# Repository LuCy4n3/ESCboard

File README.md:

# ESC_HS

This repository contains two generations of the ESC project. The repository name
remains `ESC_HS`. The original project names `ESC_HS` and `ESC_HF` are unchanged.

Both generations are experimental development builds. v1 includes firmware for
bench research and hardware bring-up; v2 is a hardware design with firmware still
to be implemented. See the [experimental build notes](v1/ESC_HS/EXPERIMENTAL_BUILD.md)
for the current v1 diagnostic configuration and validation limits.

| Version | Project | Contents | Documentation |
| --- | --- | --- | --- |
| v1 | `ESC_HS` | STSPIN32G4/STM32G431 firmware, matching KiCad design, capture tools and BOM. | [v1 usage](v1/ESC_HS/README.md) |
| v2 | `ESC_HF` | STM32H750 + DRV8323 KiCad hardware design and component libraries. | [v2 hardware](v2/ESC_HF/README.md) |

```text
ESC_HS/                         existing Git repository
  .gitignore                    shared rules for both versions
  README.md                     version index
  v1/
    ESC_HS/                     original CubeIDE project name
      Core/
      Drivers/
      esc_design/
      hardware/                 v1 BOM and review findings
      tools/
      ESC_HS.ioc
      README.md
  v2/
    ESC_HF/                     original hardware project name
      ESC_HF/                   KiCad project, schematic, PCB and Gerbers
      componente/               component symbols and footprints
      README.md
```

## Using v1

Import `v1/ESC_HS/` as the existing `ESC_HS` project in STM32CubeIDE. If an IDE
workspace still points to the old repository root, remove that workspace entry
without deleting files, then import the new directory. The project name remains
`ESC_HS`, so its workspace-relative build configuration can keep using that name.

Run the commands in the v1 usage guide from `v1/ESC_HS/`. Its schematic and BOM
links remain relative to that project directory:

- [BOM and design findings](v1/ESC_HS/hardware/BOM.md)
- [Excel BOM](v1/ESC_HS/hardware/outputs/esc_hs_bom/BOM.xlsx)
- [Grouped BOM CSV](v1/ESC_HS/hardware/BOM.csv)

The preserved v1 firmware can start with a 2000 RPM target after power-up. Review
the commissioning instructions and configuration before powering the bridge.

## Using v2

Open `v2/ESC_HF/ESC_HF/ESC_HF.kicad_pro` in KiCad. The nested hardware project and
the component-library directory retain their original names and contents.
This version currently contains hardware files. The v1 BOM and firmware describe
a different controller and power-stage design; v2 needs its own component export
and firmware implementation.

## Git organization

Both versions share this repository's existing history. Run Git commands from
this directory. Generated build files, KiCad backups/caches, source snapshots and
captures stay local under their respective version folders and are ignored.

The reorganization preserves project sources, original design files and local
build outputs. It does not change firmware behavior or hardware components.

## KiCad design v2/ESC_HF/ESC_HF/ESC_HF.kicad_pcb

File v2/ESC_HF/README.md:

# ESC_HF

**ESC v2.** The project name remains `ESC_HF`. This hardware generation uses
STM32H750 and DRV8323, with a separate schematic and PCB from
[ESC_HS v1](../../v1/ESC_HS/README.md).

This is an experimental hardware development build. Its controller and peripheral
mapping need a dedicated firmware implementation and bench validation.

## Contents

| Path | Contents |
| --- | --- |
| `ESC_HF/ESC_HF.kicad_pro` | KiCad project. |
| `ESC_HF/ESC_HF.kicad_sch` | Schematic. |
| `ESC_HF/ESC_HF.kicad_pcb` | PCB layout. |
| `componente/` | Component-library resources supplied with the design. |
| `ESC_HF/grb/`, `ESC_HF/grb.zip` | Existing manufacturing exports. |

Open `ESC_HF/ESC_HF.kicad_pro` in KiCad. Review the selected library paths when
opening the project on a different machine. Bundled 3D model links use
`${KIPRJMOD}/../componente/` so they resolve from this KiCad project after the move.
Manufacturing exports are retained
as supplied; regenerate them from the intended PCB revision before fabrication.

This directory currently contains hardware design files. It does not contain a
dedicated v2 firmware project or a newly generated v2 BOM. The v1 firmware targets
STSPIN32G4/STM32G431 and must be ported for the v2 controller and peripheral mapping.

The original schematic, circuit/layout, component resources and local backups
were preserved during version organization. Only the old absolute 3D model links
in the PCB and four footprint files were changed to project-relative paths.
Backups, lock files and caches are ignored by the
repository's shared `.gitignore`.

See the [repository version index](../../README.md) for the full layout and v1 BOM links.

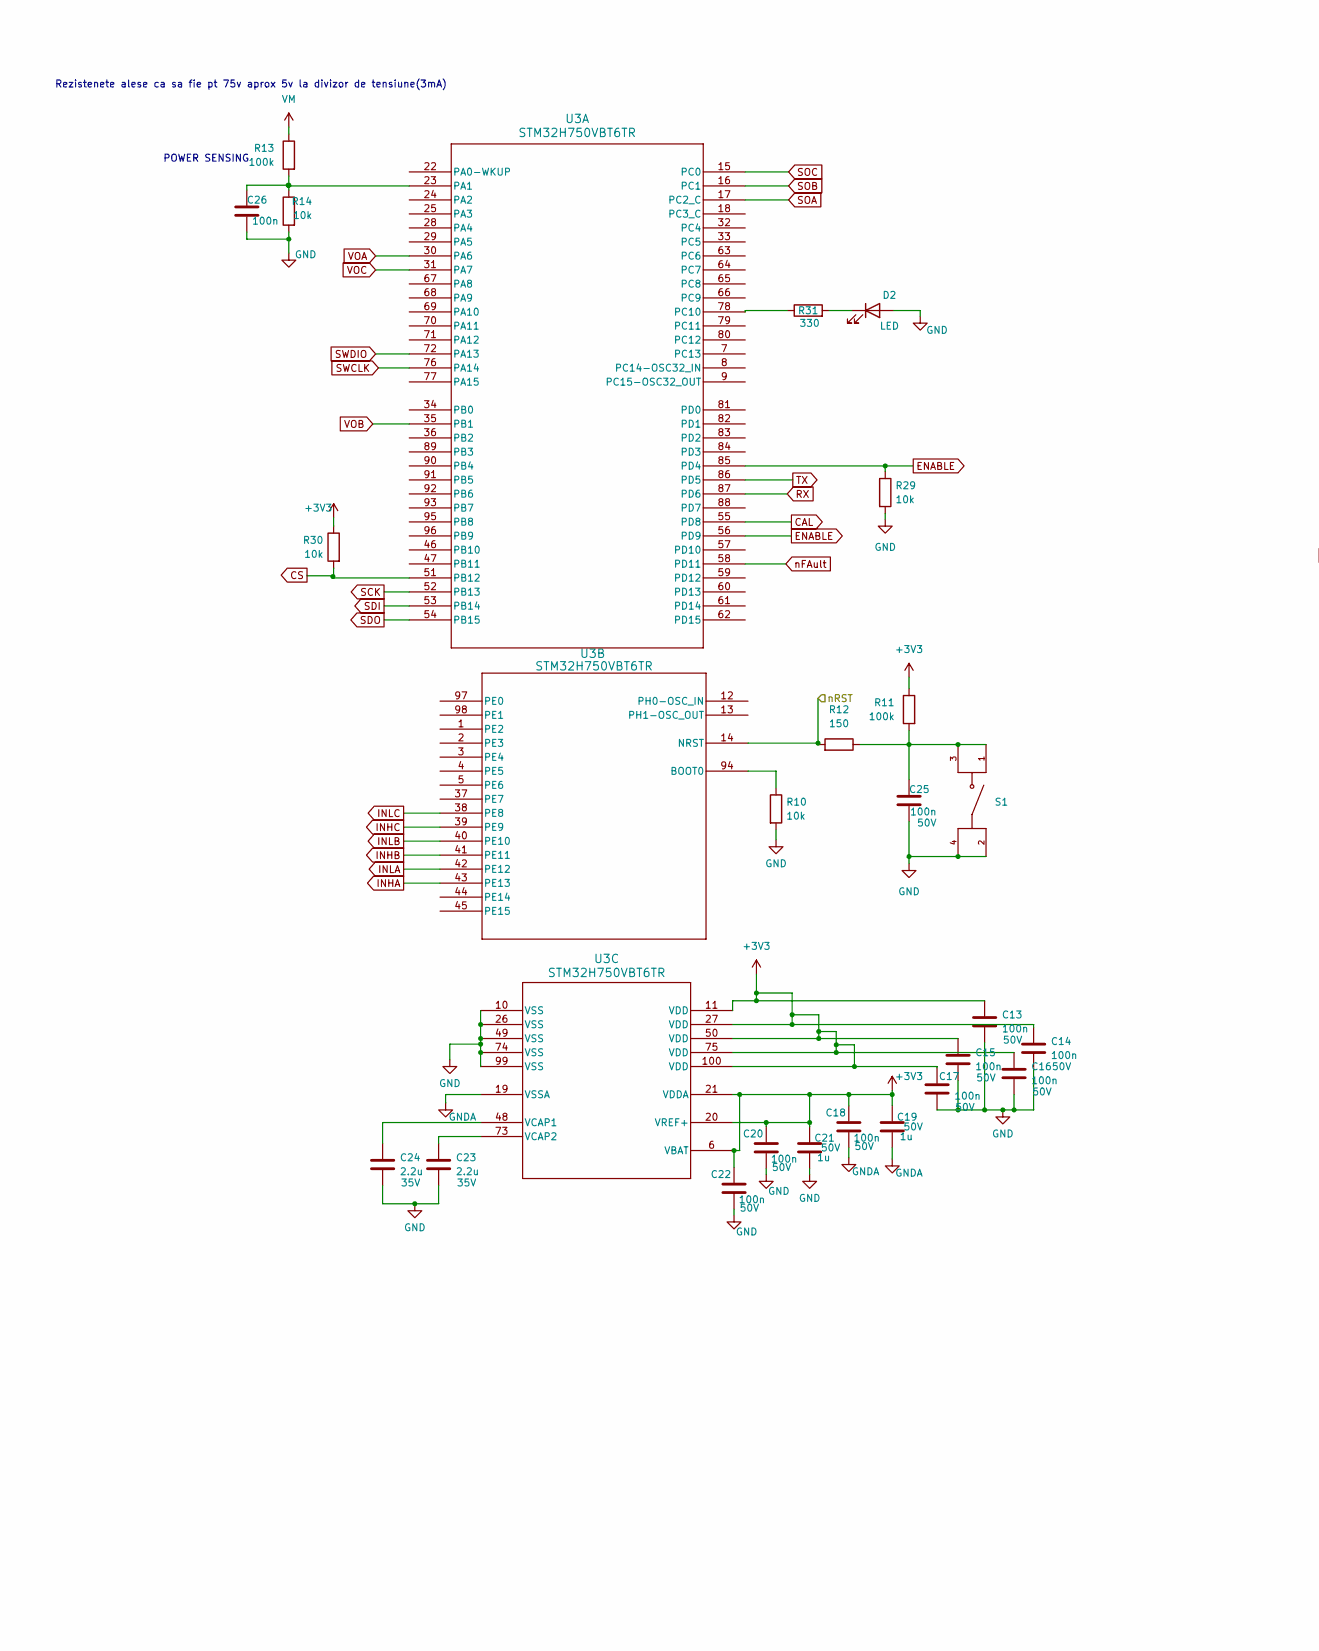
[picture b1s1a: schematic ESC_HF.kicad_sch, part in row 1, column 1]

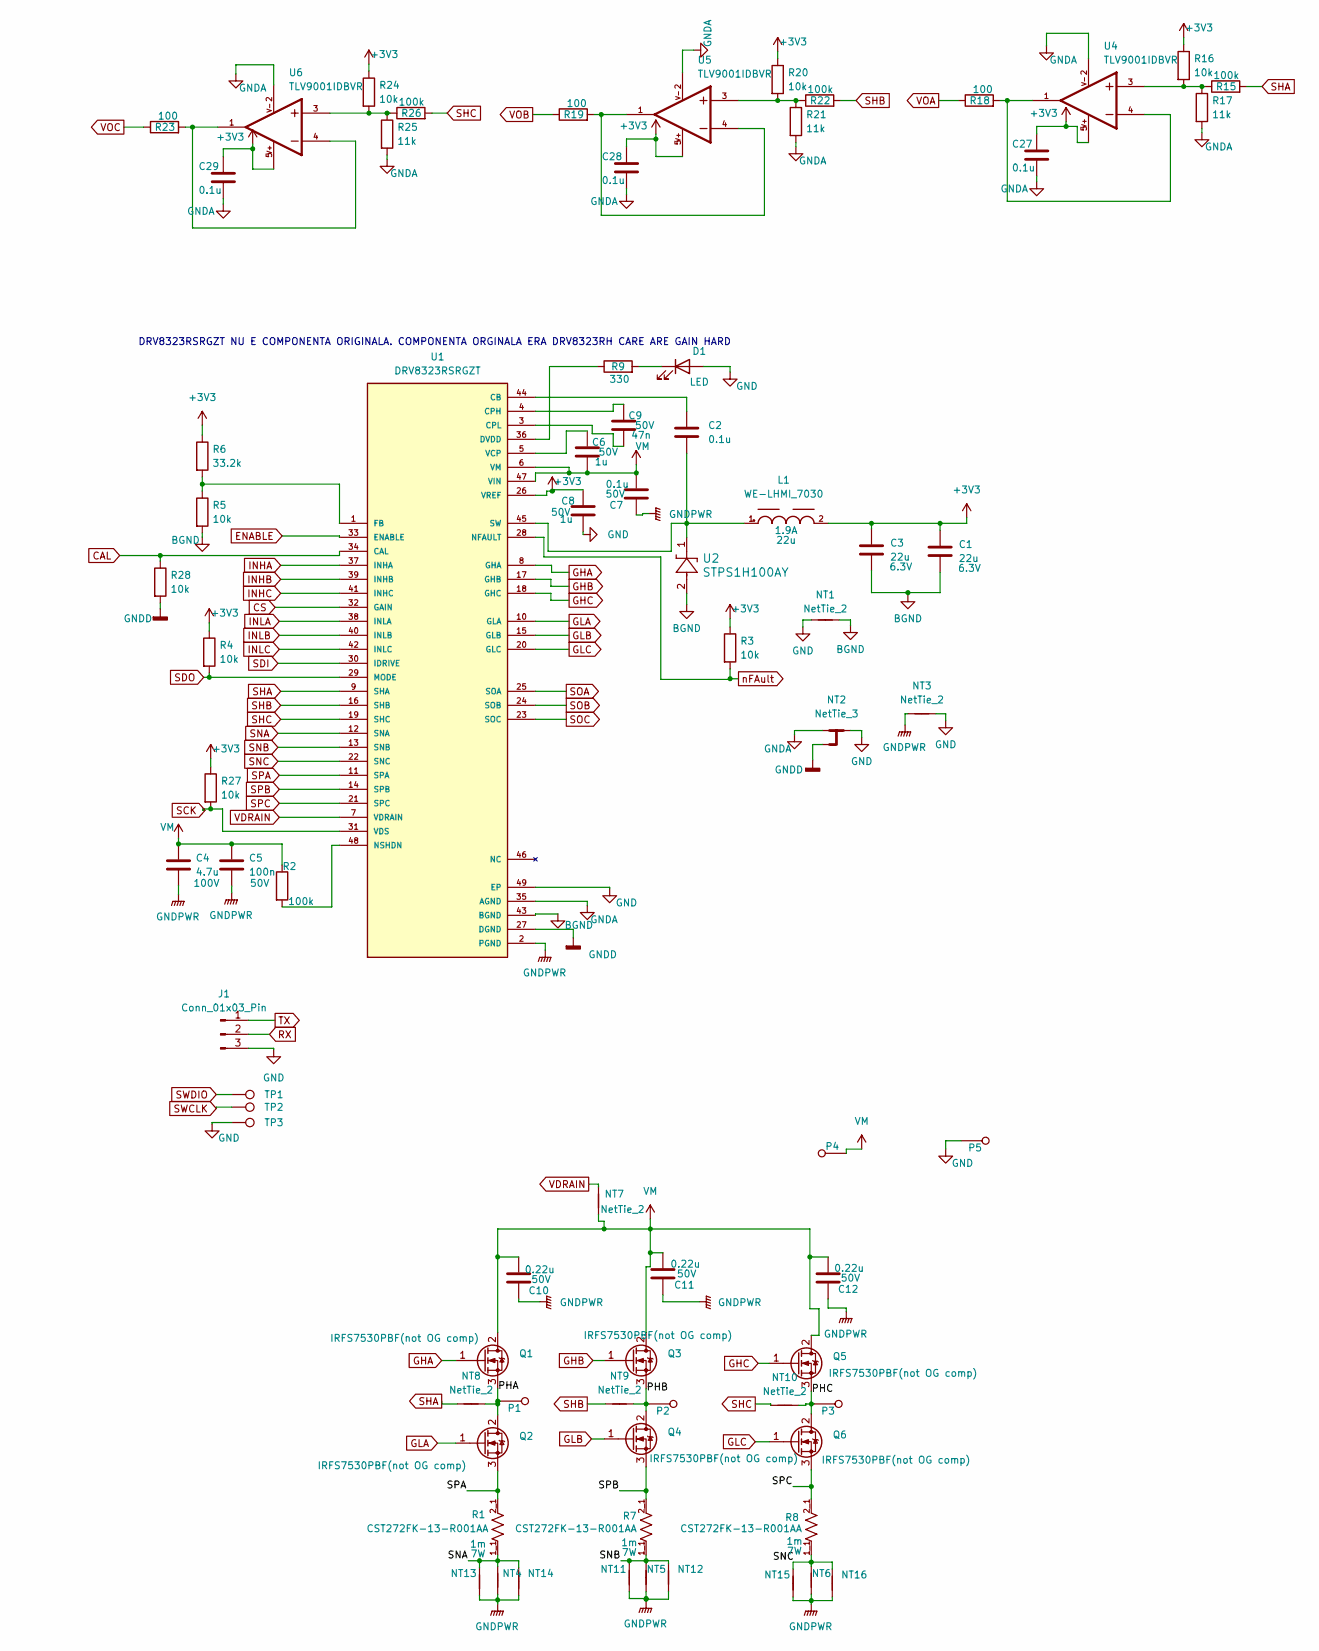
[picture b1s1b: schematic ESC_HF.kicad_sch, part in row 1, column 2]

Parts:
C1, C3: 22u; C_0603_1608Metric_Pad1.08x0.95mm_HandSolder
C2, C7, C27, C28, C29: 0.1u; C_0603_1608Metric_Pad1.08x0.95mm_HandSolder
C4: 4.7u; C_0603_1608Metric_Pad1.08x0.95mm_HandSolder
C5, C13, C14, C15, C16, C17, C18, C20, C22, C25, C26: 100n; C_0603_1608Metric_Pad1.08x0.95mm_HandSolder
C6, C8, C19, C21: 1u; C_0603_1608Metric_Pad1.08x0.95mm_HandSolder
C9: 47n; C_0603_1608Metric_Pad1.08x0.95mm_HandSolder
C10, C11, C12: 0.22u; C_0603_1608Metric_Pad1.08x0.95mm_HandSolder
C23, C24: 2.2u; C_0603_1608Metric_Pad1.08x0.95mm_HandSolder
D1, D2: LED; LED_1206_3216Metric_Pad1.42x1.75mm_HandSolder
J1: Conn_01x03_Pin; PinHeader_1x03_P2.54mm_Vertical
L1: WE-LHMI_7030
NT1, NT7: NetTie_2; NetTie-2_SMD_Pad0.5mm
NT2: NetTie_3; NetTie-3_SMD_Pad0.5mm
NT3, NT4, NT5, NT6, NT8, NT9, NT10, NT11, NT12, NT13, NT14, NT15, NT16: NetTie_2; NetTie-2_SMD_Pad2.0mm
P1, P2, P3, P4, P5: Conn_Power
Q1, Q2, Q3, Q4, Q5, Q6: IRFS7530PBF(not OG comp); TO-263-2
R1, R7, R8: CST272FK-13-R001AA; PARTREV 18-February-2025
R2, R11, R13, R15, R22, R26: 100k; R_0603_1608Metric_Pad0.98x0.95mm_HandSolder
R3, R4, R5, R10, R14, R16, R20, R24, R27, R28, R29, R30: 10k; R_0603_1608Metric_Pad0.98x0.95mm_HandSolder
R6: 33.2k; R_0603_1608Metric_Pad0.98x0.95mm_HandSolder
R9, R31: 330; R_0603_1608Metric_Pad0.98x0.95mm_HandSolder
R12: 150; R_0603_1608Metric_Pad0.98x0.95mm_HandSolder
R17, R21, R25: 11k; R_0603_1608Metric_Pad0.98x0.95mm_HandSolder
R18, R19, R23: 100; R_0603_1608Metric_Pad0.98x0.95mm_HandSolder
S1: TS04-66-43-BK-100-SMT-TR; SW_TS04-66-43-BK-100-SMT-TR
TP1, TP2, TP3: TestPoint; TestPoint_Pad_D2.0mm
U1: DRV8323RSRGZT; DRV8323RHRGZR; PARTREV AUGUST 2018
U2: STPS1H100AY; SMA_STM
U3: STM32H750VBT6TR; STM32H750VBT6
U4, U5, U6: TLV9001IDBVR; SOT95P280X145-5N; PARTREV R

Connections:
+3V3: C1.1, C3.1, C8.1, C13.1, C14.1, C15.1, C16.1, C17.1, C18.1, C19.1, C20.1, C21.1, C22.1, C27.1, C28.1, C29.1, L1.2, R3.1, R4.1, R6.1, R11.1, R16.1, R20.1, R24.1, R27.1, R30.1, U1.26 (VREF), U3.6 (VBAT), U3.11 (VDD), U3.20 (VREF+), U3.21 (VDDA), U3.27 (VDD), U3.50 (VDD), U3.75 (VDD), U3.100 (VDD), U4.5, U5.5, U6.5
/PHA: NT8.2, P1.1, Q1.3 (S), Q2.2 (D)
/PHB: NT9.2, P2.1, Q3.3 (S), Q4.2 (D)
/PHC: NT10.2, P3.1, Q5.3 (S), Q6.2 (D)
/nRST: R12.2, U3.14 (NRST)
BGND: C1.2, C3.2, NT1.2, R5.2, U1.43 (BGND), U2.2
CAL: R28.1, U1.34 (CAL), U3.55 (PD8)
CS: R30.2, U1.32 (GAIN), U3.51 (PB12)
ENABLE: R29.1, U1.33 (ENABLE), U3.56 (PD9), U3.85 (PD4)
GHA: Q1.1 (G), U1.8 (GHA)
GHB: Q3.1 (G), U1.17 (GHB)
GHC: Q5.1 (G), U1.18 (GHC)
GLA: Q2.1 (G), U1.10 (GLA)
GLB: Q4.1 (G), U1.15 (GLB)
GLC: Q6.1 (G), U1.20 (GLC)
GND: C8.2, C13.2, C14.2, C15.2, C16.2, C17.2, C20.2, C21.2, C22.2, C23.2, C24.2, C25.2, C26.2, D1.2 (A), D2.2 (A), J1.3, NT1.1, NT2.2, NT3.2, P5.1, R10.2, R14.2, R29.2, S1.2, S1.4, TP3.1, U1.49 (EP), U1.V49_1 (EP), U1.V49_2 (EP), U1.V49_3 (EP), U1.V49_4 (EP), U1.V49_5 (EP), U1.V49_6 (EP), U1.V49_7 (EP), U1.V49_8 (EP), U1.V49_9 (EP), U1.V49_10 (EP), U1.V49_11 (EP), U1.V49_12 (EP), U1.V49_13 (EP), U1.V49_14 (EP), U1.V49_15 (EP), U1.V49_16 (EP), U1.V49_17 (EP), U1.V49_18 (EP), U1.V49_19 (EP), U1.V49_20 (EP), U1.V49_21 (EP), U3.10 (VSS), U3.26 (VSS), U3.49 (VSS), U3.74 (VSS), U3.99 (VSS)
GNDA: C18.2, C19.2, C27.2, C28.2, C29.2, NT2.1, R17.2, R21.2, R25.2, U1.35 (AGND), U3.19 (VSSA), U4.2, U5.2, U6.2
GNDD: NT2.3, R28.2, U1.27 (DGND)
GNDPWR: C4.2, C5.2, C7.1, C10.1, C11.1, C12.1, NT3.1, NT4.1, NT5.1, NT6.1, NT11.2, NT12.2, NT13.2, NT14.2, NT15.2, NT16.2, U1.2 (PGND)
INHA: U1.37 (INHA), U3.43 (PE13)
INHB: U1.39 (INHB), U3.41 (PE11)
INHC: U1.41 (INHC), U3.39 (PE9)
INLA: U1.38 (INLA), U3.42 (PE12)
INLB: U1.40 (INLB), U3.40 (PE10)
INLC: U1.42 (INLC), U3.38 (PE8)
unnamed: C25.1, R11.2, R12.1, S1.1, S1.3
unnamed: D1.1 (K), R9.2
unnamed: D2.1 (K), R31.2
unnamed: R15.1, R16.2, R17.1, U4.3
unnamed: R18.2, U4.1, U4.4
unnamed: R19.2, U5.1, U5.4
unnamed: R20.2, R21.1, R22.1, U5.3
unnamed: R23.2, U6.1, U6.4
unnamed: R24.2, R25.1, R26.1, U6.3
unnamed: C2.1, U1.44 (CB)
unnamed: C9.1, U1.4 (CPH)
unnamed: C9.2, U1.3 (CPL)
unnamed: R9.1, U1.36 (DVDD)
unnamed: R5.1, R6.2, U1.1 (FB)
unnamed: R2.2, U1.48 (NSHDN)
unnamed: C2.2, L1.1, U1.45 (SW), U2.1
unnamed: C6.1, U1.5 (VCP)
unnamed: C26.1, R13.2, R14.1, U3.23 (PA1)
unnamed: R31.1, U3.78 (PC10)
unnamed: R10.1, U3.94 (BOOT0)
unnamed: C24.1, U3.48 (VCAP1)
unnamed: C23.1, U3.73 (VCAP2)
RX: J1.2, U3.87 (PD6)
SCK: R27.2, U1.31 (VDS), U3.52 (PB13)
SDI: U1.30 (IDRIVE), U3.53 (PB14)
SDO: R4.2, U1.29 (MODE), U3.54 (PB15)
SHA: NT8.1, R15.2, U1.9 (SHA)
SHB: NT9.1, R22.2, U1.16 (SHB)
SHC: NT10.1, R26.2, U1.19 (SHC)
SNA: NT4.2, NT13.1, NT14.1, R1.1_1, R1.1_2, U1.12 (SNA)
SNB: NT5.2, NT11.1, NT12.1, R7.1_1, R7.1_2, U1.13 (SNB)
SNC: NT6.2, NT15.1, NT16.1, R8.1_1, R8.1_2, U1.22 (SNC)
SOA: U1.25 (SOA), U3.17 (PC2_C)
SOB: U1.24 (SOB), U3.16 (PC1)
SOC: U1.23 (SOC), U3.15 (PC0)
SPA: Q2.3 (S), R1.2_1, R1.2_2, U1.11 (SPA)
SPB: Q4.3 (S), R7.2_1, R7.2_2, U1.14 (SPB)
SPC: Q6.3 (S), R8.2_1, R8.2_2, U1.21 (SPC)
SWCLK: TP2.1, U3.76 (PA14)
SWDIO: TP1.1, U3.72 (PA13)
TX: J1.1, U3.86 (PD5)
VDRAIN: NT7.2, U1.7 (VDRAIN)
VM: C4.1, C5.1, C6.2, C7.2, C10.2, C11.2, C12.2, NT7.1, P4.1, Q1.2 (D), Q3.2 (D), Q5.2 (D), R2.1, R13.1, U1.6 (VM), U1.47 (VIN)
VOA: R18.1, U3.30 (PA6)
VOB: R19.1, U3.35 (PB1)
VOC: R23.1, U3.31 (PA7)
nFAult: R3.2, U1.28 (NFAULT), U3.58 (PD11)

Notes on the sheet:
POWER SENSING
Rezistenete alese ca sa fie pt 75v aprox 5v la divizor de tensiune(3mA)
DRV8323RSRGZT NU E COMPONENTA ORIGINALA. COMPONENTA ORGINALA ERA DRV8323RH CARE ARE GAIN HARD

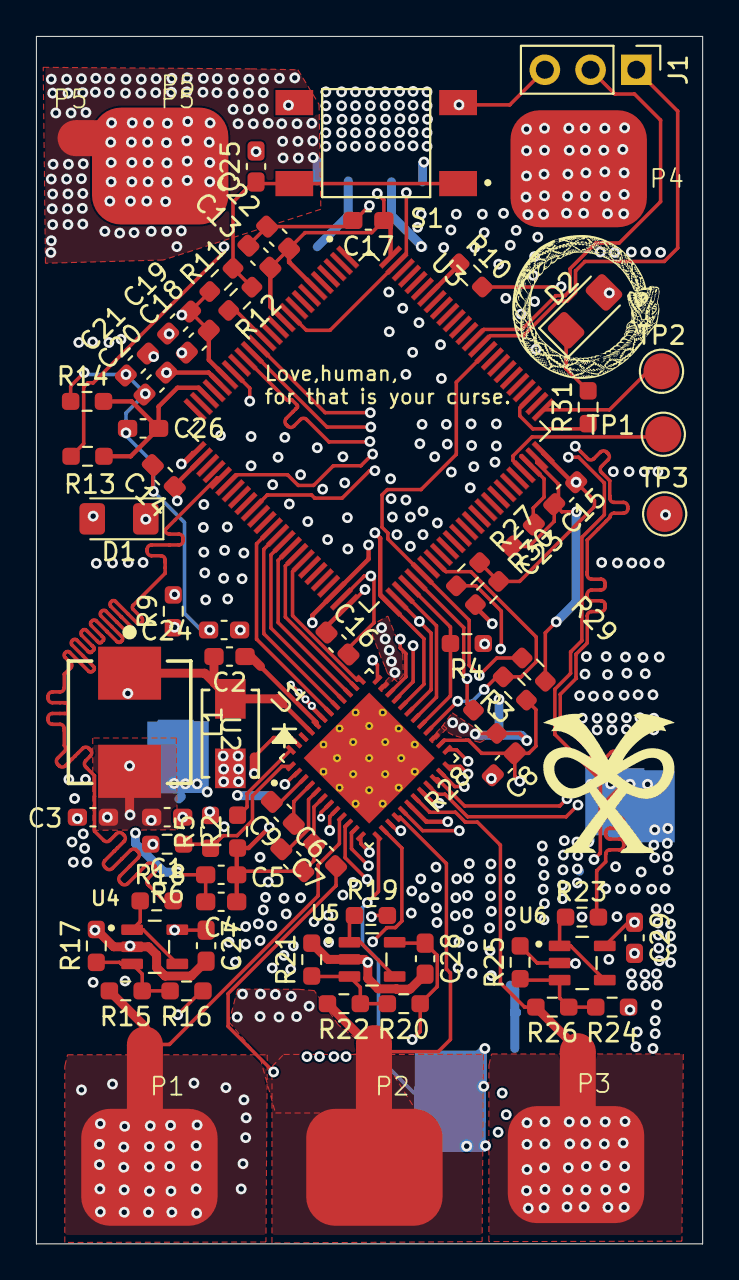
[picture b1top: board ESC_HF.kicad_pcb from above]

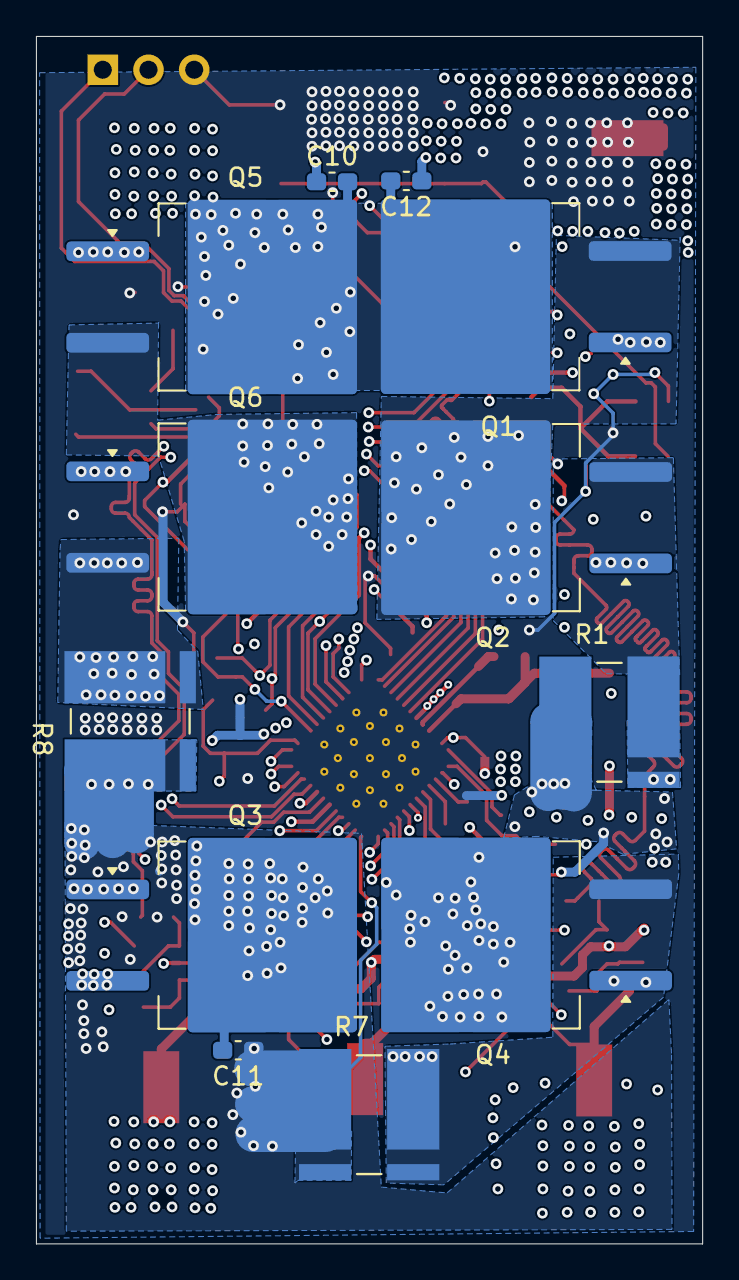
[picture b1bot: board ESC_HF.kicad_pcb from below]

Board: 6 copper layers, 37.0 x 67.1 mm, 101 parts (23 on the bottom side), 72 nets.
